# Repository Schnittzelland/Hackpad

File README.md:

# Hackpad by Fabian
My 15 Key Hackpad build with an OLED Display to keep track of your Uptime.
# Features
- 15x Keys
- 128*32 OLED Display with displayable uptime
# PCB and Schematic
Here are my Pictures of my PCB and Schematic

# CAD

The Top of the Case is connected via 4 Screws. The PCB itselfs is also connected to the Case itself

# Firmware
The firmware is made with QMK. The Keys have no function at the moment but i will use them for macros or for additional keys for video games. The OLED Screen will show you your current uptime.

# BOM
- 1 SEEEDUINO XIAO RP2040
- 15x MX-Style switches
- 5x 1N4148 Diodes
- 8x M3x16mm screws
- 1x 0.91 inch OLED displays
- 1x 3D-Printed Case

# Bonus 
This is my first time doing something like this. I really enjoyed making all the things espacially wiring the PCB. I really hope that the Firmware works as intentendet, if not i will try to fix it.

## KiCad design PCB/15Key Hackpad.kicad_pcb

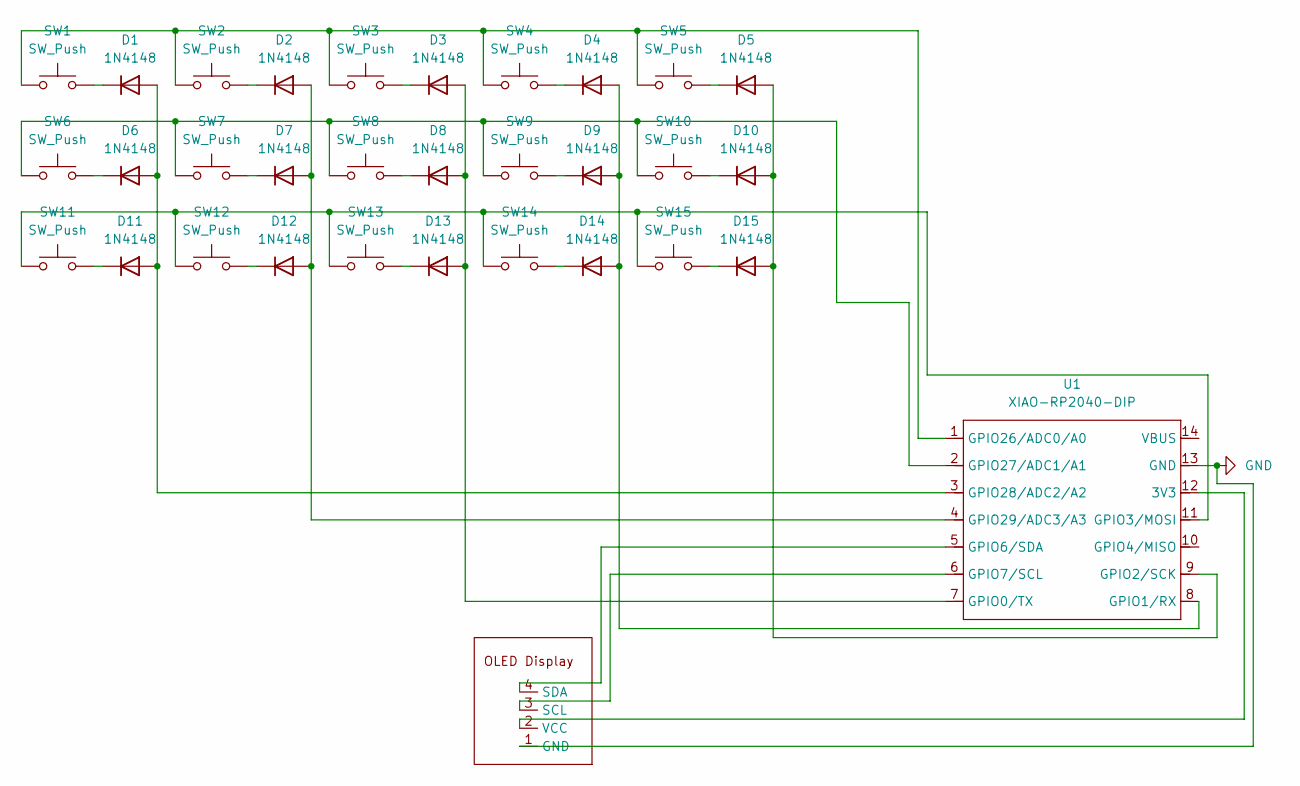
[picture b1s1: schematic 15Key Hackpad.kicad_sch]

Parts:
D1, D2, D3, D4, D5, D6, D7, D8, D9, D10, D11, D12, D13, D14, D15: 1N4148; D_DO-35_SOD27_P7.62mm_Horizontal
SW1, SW2, SW3, SW4, SW5, SW6, SW7, SW8, SW9, SW10, SW11, SW12, SW13, SW14, SW15: SW_Push; SW_Cherry_MX_1.00u_PCB
U1: XIAO-RP2040-DIP
U2: OLED Display; SSD1306-0.91-OLED-4pin-128x32

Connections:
GND: U1.13 (GND), U2.1 (GND)
unnamed: D1.2 (A), D6.2 (A), D11.2 (A), U1.3 (GPIO28/ADC2/A2)
unnamed: D1.1 (K), SW1.2
unnamed: D2.1 (K), SW2.2
unnamed: D3.1 (K), SW3.2
unnamed: D4.1 (K), SW4.2
unnamed: D5.1 (K), SW5.2
unnamed: D6.1 (K), SW6.2
unnamed: D7.1 (K), SW7.2
unnamed: D8.1 (K), SW8.2
unnamed: D9.1 (K), SW9.2
unnamed: D5.2 (A), D10.2 (A), D15.2 (A), U1.9 (GPIO2/SCK)
unnamed: D10.1 (K), SW10.2
unnamed: D11.1 (K), SW11.2
unnamed: D2.2 (A), D7.2 (A), D12.2 (A), U1.4 (GPIO29/ADC3/A3)
unnamed: D12.1 (K), SW12.2
unnamed: D3.2 (A), D8.2 (A), D13.2 (A), U1.7 (GPIO0/TX)
unnamed: D13.1 (K), SW13.2
unnamed: D4.2 (A), D9.2 (A), D14.2 (A), U1.8 (GPIO1/RX)
unnamed: D14.1 (K), SW14.2
unnamed: D15.1 (K), SW15.2
unnamed: U1.12 (3V3), U2.2 (VCC)
unnamed: SW11.1, SW12.1, SW13.1, SW14.1, SW15.1, U1.11 (GPIO3/MOSI)
unnamed: U1.5 (GPIO6/SDA), U2.4 (SDA)
unnamed: U1.6 (GPIO7/SCL), U2.3 (SCL)
unnamed: SW1.1, SW2.1, SW3.1, SW4.1, SW5.1, U1.1 (GPIO26/ADC0/A0)
unnamed: SW6.1, SW7.1, SW8.1, SW9.1, SW10.1, U1.2 (GPIO27/ADC1/A1)

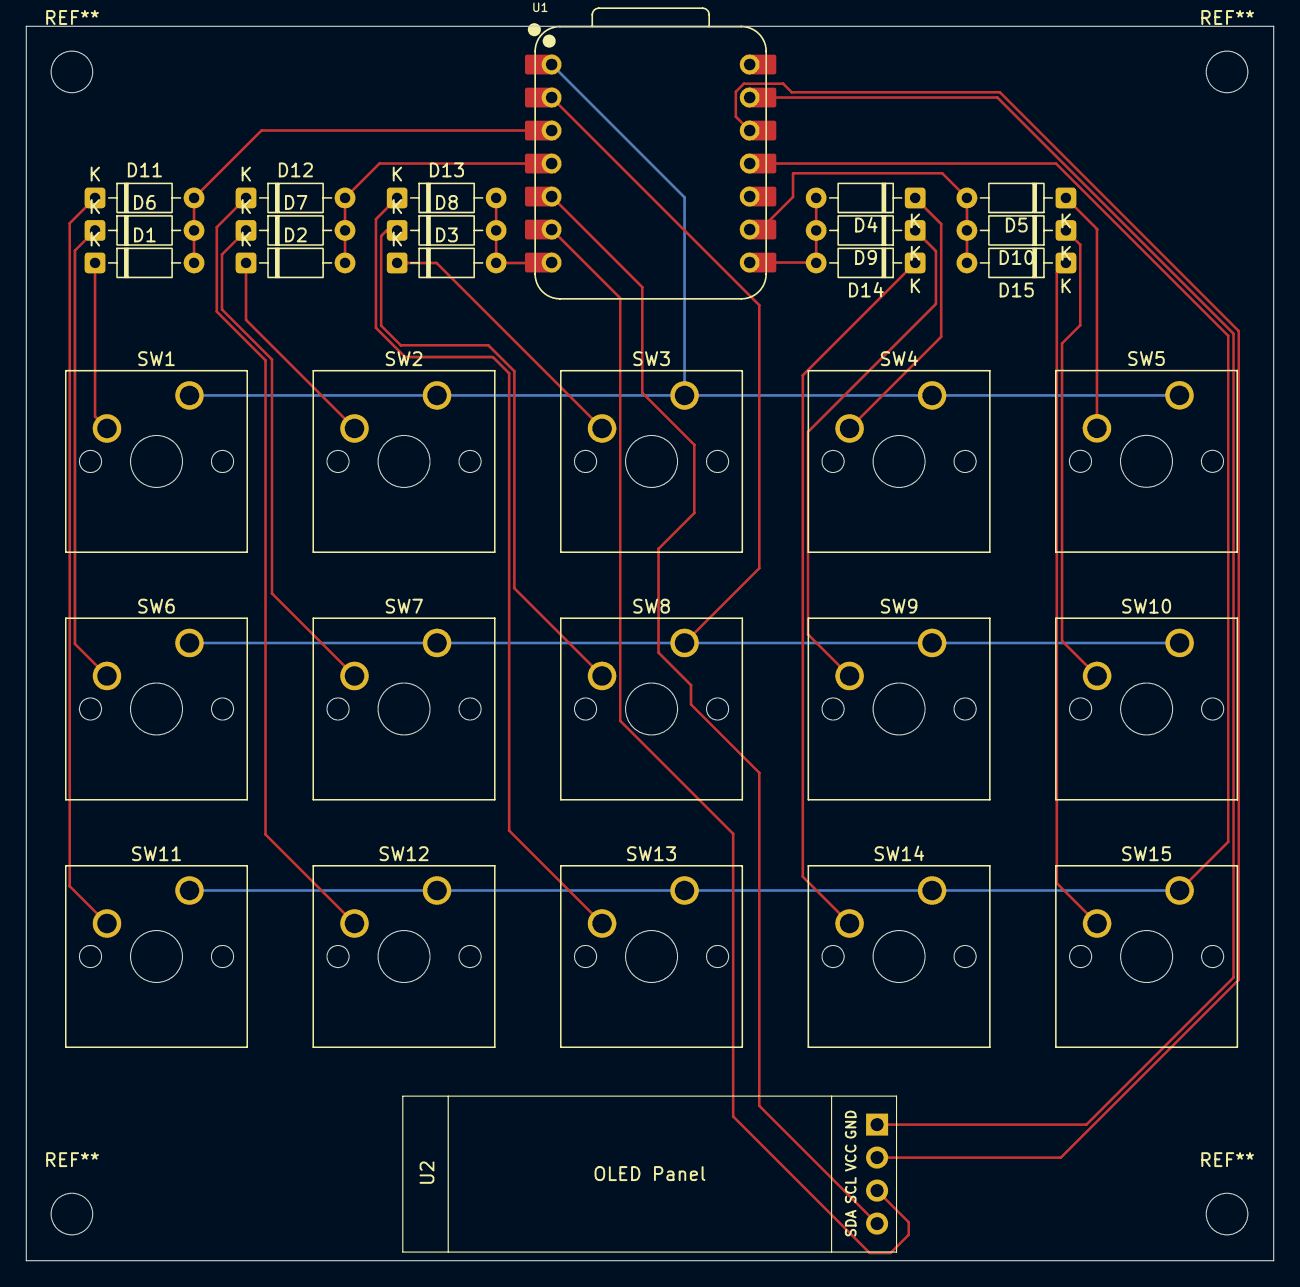
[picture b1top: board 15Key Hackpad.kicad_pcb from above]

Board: 2 copper layers, 96.0 x 95.0 mm, 32 parts (0 on the bottom side), 27 nets.

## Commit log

2026-01-16 approved Version
2026-01-16 Picture
